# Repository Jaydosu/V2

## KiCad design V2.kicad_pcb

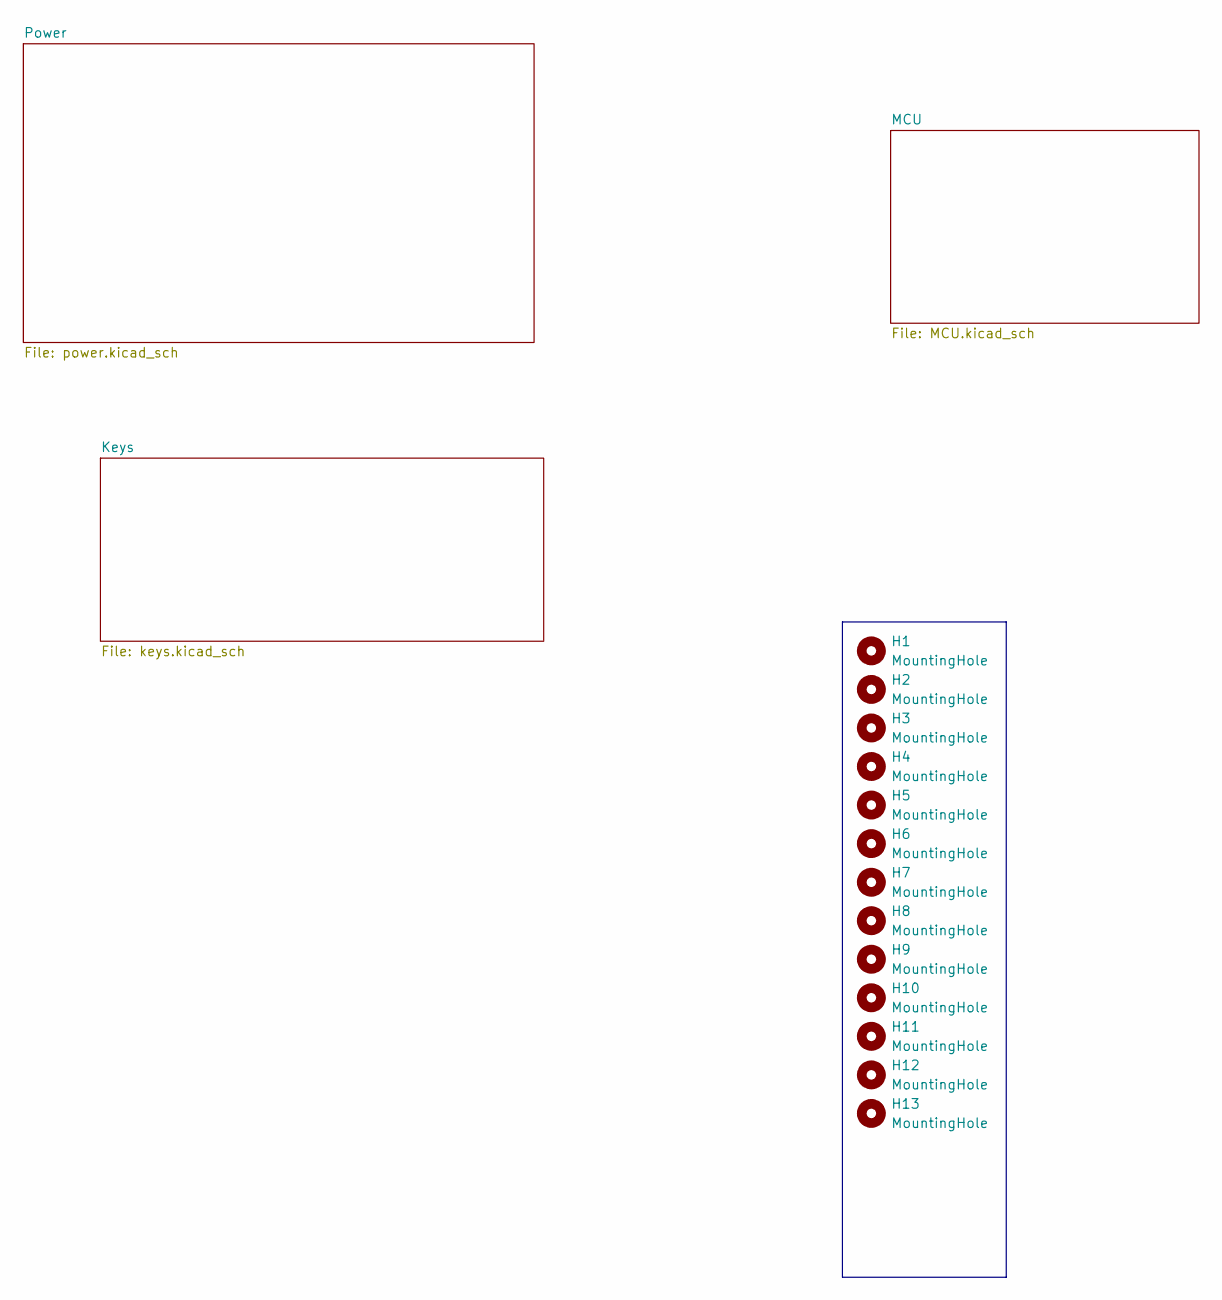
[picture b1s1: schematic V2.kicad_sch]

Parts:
H1, H2, H3, H4, H5, H6, H7, H8, H9, H10, H11, H12, H13: MountingHole; MountingHole_3.2mm_M3_Pad

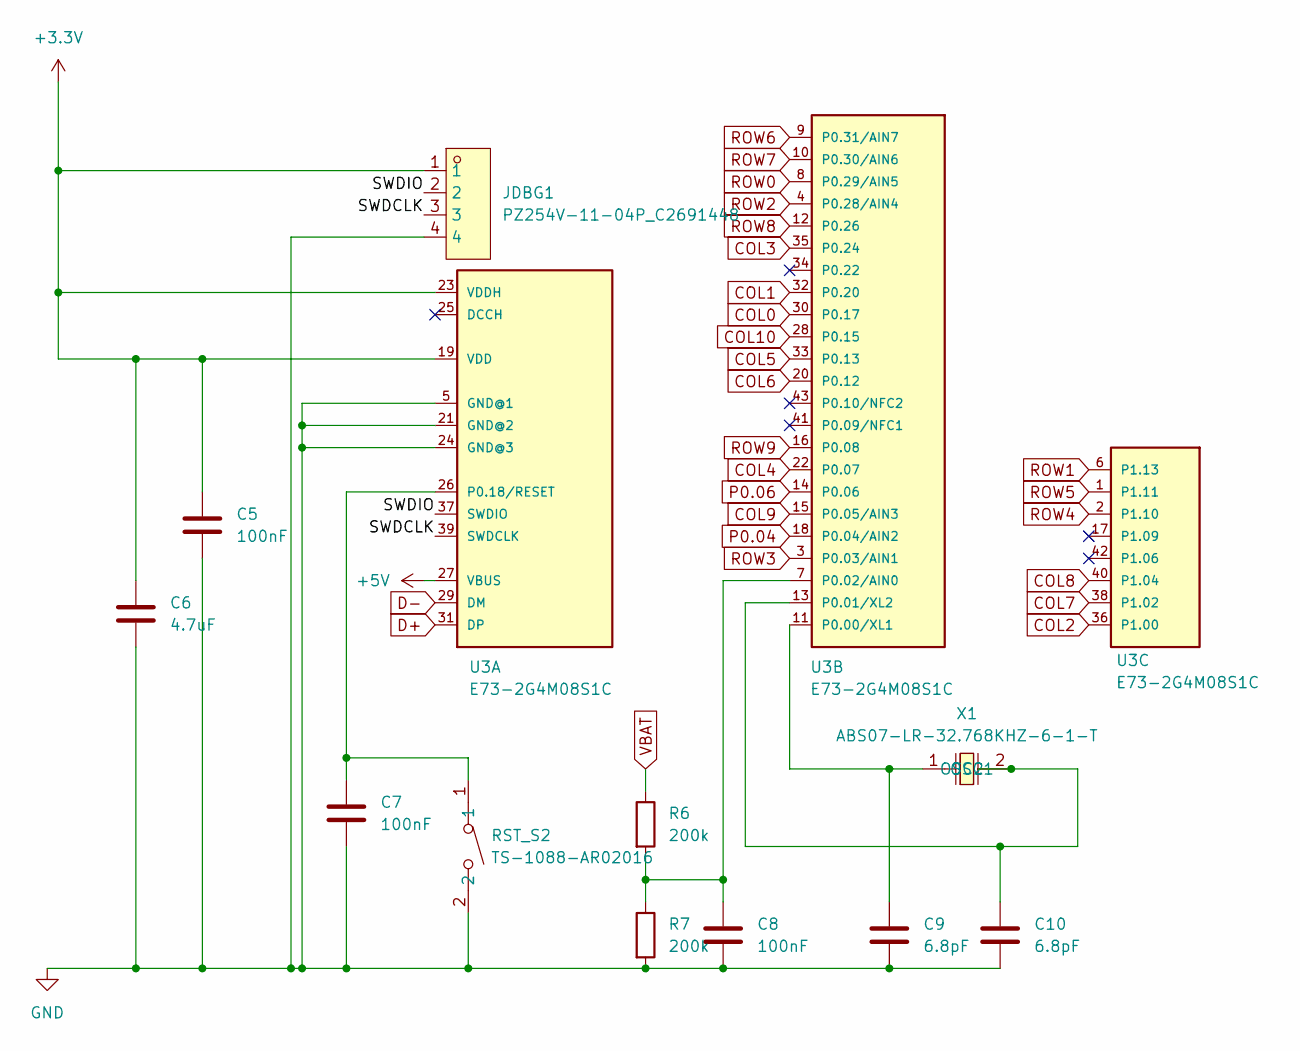
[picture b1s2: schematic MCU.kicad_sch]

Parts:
C5, C7, C8: 100nF; C_0603_1608Metric; LCSC Part C14663
C6: 4.7uF; C_0603_1608Metric; LCSC Part C19666
C9, C10: 6.8pF; C_0603_1608Metric; LCSC Part C1679
JDBG1: PZ254V-11-04P_C2691448; HDR-TH_4P-P2.54-V-M; MPN PZ254V-11-04P; LCSC Part C2691448
R6, R7: 200k; R_0603_1608Metric; LCSC Part C25811
RST_S2: TS-1088-AR02016; SW-SMD_L3.9-W3.0-P4.45; MPN TS-1088-AR02016; LCSC Part C720477
U3: E73-2G4M08S1C; LCSC Part C356849
X1: ABS07-LR-32.768KHZ-6-1-T; CRYSTAL-SMD_L3.2-W1.5; MPN ABS07-LR-32.768KHZ-6-1-T; LCSC Part C6491652

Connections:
+3.3V: C5.2, C6.1, JDBG1.1, U3.19 (VDD), U3.23 (VDDH); also elsewhere on the board
+5V: U3.27 (VBUS); also elsewhere on the board
/MCU/SWDCLK: JDBG1.3, U3.39 (SWDCLK)
/MCU/SWDIO: JDBG1.2, U3.37 (SWDIO)
COL0: U3.30 (P0.17); also elsewhere on the board
COL1: U3.32 (P0.20); also elsewhere on the board
COL2: U3.36 (P1.00); also elsewhere on the board
COL3: U3.35 (P0.24); also elsewhere on the board
COL4: U3.22 (P0.07); also elsewhere on the board
COL5: U3.33 (P0.13); also elsewhere on the board
COL6: U3.20 (P0.12); also elsewhere on the board
COL7: U3.38 (P1.02); also elsewhere on the board
COL8: U3.40 (P1.04); also elsewhere on the board
COL9: U3.15 (P0.05/AIN3); also elsewhere on the board
COL10: U3.28 (P0.15); also elsewhere on the board
D+: U3.31 (DP); also elsewhere on the board
D-: U3.29 (DM); also elsewhere on the board
GND: C5.1, C6.2, C7.2, C8.2, C9.2, C10.2, JDBG1.4, R7.2, RST_S2.2, U3.5 (GND@1), U3.21 (GND@2), U3.24 (GND@3); also elsewhere on the board
unnamed: C7.1, RST_S2.1, U3.26 (P0.18/RESET)
unnamed: C9.1, U3.11 (P0.00/XL1), X1.1 (OSC1)
unnamed: C10.1, U3.13 (P0.01/XL2), X1.2 (OSC2)
unnamed: C8.1, R6.2, R7.1, U3.7 (P0.02/AIN0)
P0.04: U3.18 (P0.04/AIN2); also elsewhere on the board
P0.06: U3.14 (P0.06); also elsewhere on the board
ROW0: U3.8 (P0.29/AIN5); also elsewhere on the board
ROW1: U3.6 (P1.13); also elsewhere on the board
ROW2: U3.4 (P0.28/AIN4); also elsewhere on the board
ROW3: U3.3 (P0.03/AIN1); also elsewhere on the board
ROW4: U3.2 (P1.10); also elsewhere on the board
ROW5: U3.1 (P1.11); also elsewhere on the board
ROW6: U3.9 (P0.31/AIN7); also elsewhere on the board
ROW7: U3.10 (P0.30/AIN6); also elsewhere on the board
ROW8: U3.12 (P0.26); also elsewhere on the board
ROW9: U3.16 (P0.08); also elsewhere on the board
VBAT: R6.1; also elsewhere on the board

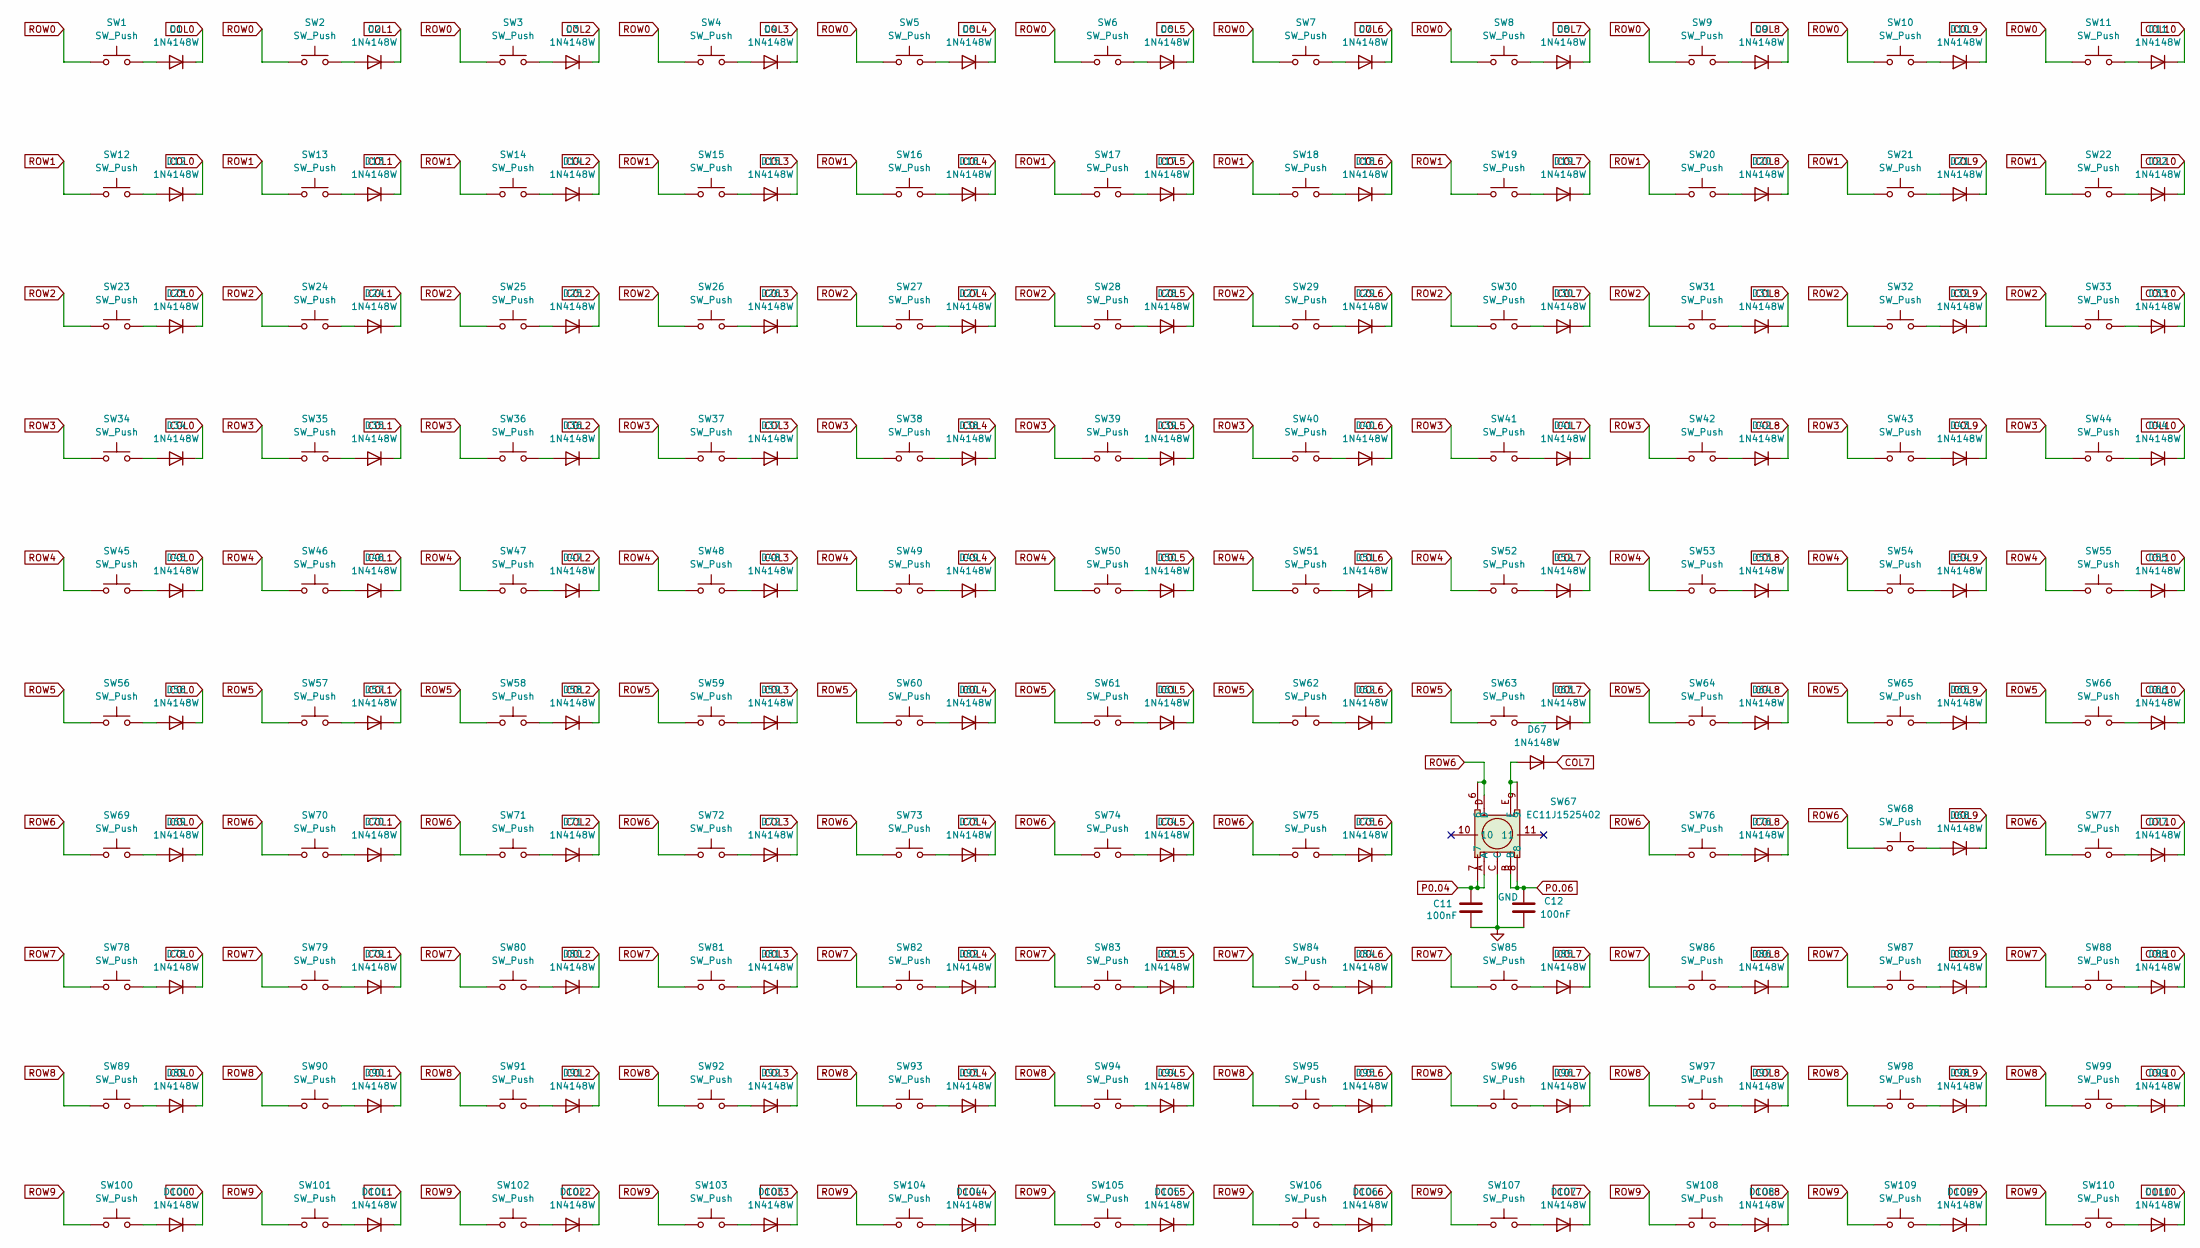
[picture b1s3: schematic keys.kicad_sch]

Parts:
C11, C12: 100nF; C_0603_1608Metric; LCSC Part C14663
D1, D2, D3, D4, D5, D6, D7, D8, D9, D10, D11, D12, D13, D14, D15, D16, D17, D18, D19, D20, D21, D22, D23, D24, D25, D26, D27, D28, D29, D30, D31, D32, D33, D34, D35, D36, D37, D38, D39, D40, D41, D42, D43, D44, D45, D46, D47, D48, D49, D50, D51, D52, D53, D54, D55, D56, D57, D58, D59, D60, D61, D62, D63, D64, D65, D66, D67, D68, D69, D70, D71, D72, D73, D74, D75, D76, D77, D78, D79, D80, D81, D82, D83, D84, D85, D86, D87, D88, D89, D90, D91, D92, D93, D94, D95, D96, D97, D98, D99, D100, D101, D102, D103, D104, D105, D106, D107, D108, D109, D110: 1N4148W; D_SOD-123; LCSC Part C81598
SW1, SW2, SW3, SW4, SW5, SW6, SW7, SW8, SW9, SW10, SW11, SW12, SW13, SW14, SW15, SW16, SW17, SW18, SW19, SW20, SW21, SW22, SW23, SW24, SW25, SW26, SW27, SW28, SW29, SW30, SW31, SW32, SW33, SW34, SW35, SW36, SW37, SW38, SW39, SW40, SW41, SW42, SW43, SW44, SW45, SW46, SW47, SW48, SW49, SW50, SW51, SW52, SW53, SW54, SW55, SW56, SW57, SW58, SW59, SW60, SW61, SW62, SW63, SW64, SW65, SW66, SW68, SW69, SW70, SW71, SW72, SW73, SW74, SW75, SW76, SW77, SW78, SW79, SW80, SW81, SW82, SW83, SW84, SW85, SW86, SW87, SW88, SW89, SW90, SW91, SW92, SW93, SW94, SW95, SW96, SW97, SW98, SW99, SW100, SW101, SW102, SW103, SW104, SW105, SW106, SW107, SW108, SW109, SW110: SW_Push; SW_Hotswap_Kailh_MX_Plated; LCSC Part C41430893
SW67: EC11J1525402; SW-SMD_EC11J1525402; MPN EC11J1525402; LCSC Part C209762

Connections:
COL0: D1.1 (K), D12.1 (K), D23.1 (K), D34.1 (K), D45.1 (K), D56.1 (K), D69.1 (K), D78.1 (K), D89.1 (K), D100.1 (K); also elsewhere on the board
COL1: D2.1 (K), D13.1 (K), D24.1 (K), D35.1 (K), D46.1 (K), D57.1 (K), D70.1 (K), D79.1 (K), D90.1 (K), D101.1 (K); also elsewhere on the board
COL2: D3.1 (K), D14.1 (K), D25.1 (K), D36.1 (K), D47.1 (K), D58.1 (K), D71.1 (K), D80.1 (K), D91.1 (K), D102.1 (K); also elsewhere on the board
COL3: D4.1 (K), D15.1 (K), D26.1 (K), D37.1 (K), D48.1 (K), D59.1 (K), D72.1 (K), D81.1 (K), D92.1 (K), D103.1 (K); also elsewhere on the board
COL4: D5.1 (K), D16.1 (K), D27.1 (K), D38.1 (K), D49.1 (K), D60.1 (K), D73.1 (K), D82.1 (K), D93.1 (K), D104.1 (K); also elsewhere on the board
COL5: D6.1 (K), D17.1 (K), D28.1 (K), D39.1 (K), D50.1 (K), D61.1 (K), D74.1 (K), D83.1 (K), D94.1 (K), D105.1 (K); also elsewhere on the board
COL6: D7.1 (K), D18.1 (K), D29.1 (K), D40.1 (K), D51.1 (K), D62.1 (K), D75.1 (K), D84.1 (K), D95.1 (K), D106.1 (K); also elsewhere on the board
COL7: D8.1 (K), D19.1 (K), D30.1 (K), D41.1 (K), D52.1 (K), D63.1 (K), D67.1 (K), D85.1 (K), D96.1 (K), D107.1 (K); also elsewhere on the board
COL8: D9.1 (K), D20.1 (K), D31.1 (K), D42.1 (K), D53.1 (K), D64.1 (K), D76.1 (K), D86.1 (K), D97.1 (K), D108.1 (K); also elsewhere on the board
COL9: D10.1 (K), D21.1 (K), D32.1 (K), D43.1 (K), D54.1 (K), D65.1 (K), D68.1 (K), D87.1 (K), D98.1 (K), D109.1 (K); also elsewhere on the board
COL10: D11.1 (K), D22.1 (K), D33.1 (K), D44.1 (K), D55.1 (K), D66.1 (K), D77.1 (K), D88.1 (K), D99.1 (K), D110.1 (K); also elsewhere on the board
GND: C11.2, C12.2, SW67.C; also elsewhere on the board
unnamed: D1.2 (A), SW1.2
unnamed: D2.2 (A), SW2.2
unnamed: D3.2 (A), SW3.2
unnamed: D4.2 (A), SW4.2
unnamed: D5.2 (A), SW5.2
unnamed: D6.2 (A), SW6.2
unnamed: D7.2 (A), SW7.2
unnamed: D8.2 (A), SW8.2
unnamed: D9.2 (A), SW9.2
unnamed: D10.2 (A), SW10.2
unnamed: D11.2 (A), SW11.2
unnamed: D12.2 (A), SW12.2
unnamed: D13.2 (A), SW13.2
unnamed: D14.2 (A), SW14.2
unnamed: D15.2 (A), SW15.2
unnamed: D16.2 (A), SW16.2
unnamed: D17.2 (A), SW17.2
unnamed: D18.2 (A), SW18.2
unnamed: D19.2 (A), SW19.2
unnamed: D20.2 (A), SW20.2
unnamed: D21.2 (A), SW21.2
unnamed: D22.2 (A), SW22.2
unnamed: D23.2 (A), SW23.2
unnamed: D24.2 (A), SW24.2
unnamed: D25.2 (A), SW25.2
unnamed: D26.2 (A), SW26.2
unnamed: D27.2 (A), SW27.2
unnamed: D28.2 (A), SW28.2
unnamed: D29.2 (A), SW29.2
unnamed: D30.2 (A), SW30.2
unnamed: D31.2 (A), SW31.2
unnamed: D32.2 (A), SW32.2
unnamed: D33.2 (A), SW33.2
unnamed: D34.2 (A), SW34.2
unnamed: D35.2 (A), SW35.2
unnamed: D36.2 (A), SW36.2
unnamed: D37.2 (A), SW37.2
unnamed: D38.2 (A), SW38.2
unnamed: D39.2 (A), SW39.2
unnamed: D40.2 (A), SW40.2
unnamed: D41.2 (A), SW41.2
unnamed: D42.2 (A), SW42.2
unnamed: D43.2 (A), SW43.2
unnamed: D44.2 (A), SW44.2
unnamed: D45.2 (A), SW45.2
unnamed: D46.2 (A), SW46.2
unnamed: D47.2 (A), SW47.2
unnamed: D48.2 (A), SW48.2
unnamed: D49.2 (A), SW49.2
unnamed: D50.2 (A), SW50.2
unnamed: D51.2 (A), SW51.2
unnamed: D52.2 (A), SW52.2
unnamed: D53.2 (A), SW53.2
unnamed: D54.2 (A), SW54.2
unnamed: D55.2 (A), SW55.2
unnamed: D56.2 (A), SW56.2
unnamed: D57.2 (A), SW57.2
unnamed: D58.2 (A), SW58.2
unnamed: D59.2 (A), SW59.2
unnamed: D60.2 (A), SW60.2
unnamed: D61.2 (A), SW61.2
unnamed: D62.2 (A), SW62.2
unnamed: D63.2 (A), SW63.2
unnamed: D64.2 (A), SW64.2
unnamed: D65.2 (A), SW65.2
unnamed: D66.2 (A), SW66.2
unnamed: D67.2 (A), SW67.9, SW67.E
unnamed: D68.2 (A), SW68.2
unnamed: D69.2 (A), SW69.2
unnamed: D70.2 (A), SW70.2
unnamed: D71.2 (A), SW71.2
unnamed: D72.2 (A), SW72.2
unnamed: D73.2 (A), SW73.2
unnamed: D74.2 (A), SW74.2
unnamed: D75.2 (A), SW75.2
unnamed: D76.2 (A), SW76.2
unnamed: D77.2 (A), SW77.2
unnamed: D78.2 (A), SW78.2
unnamed: D79.2 (A), SW79.2
unnamed: D80.2 (A), SW80.2
unnamed: D81.2 (A), SW81.2
unnamed: D82.2 (A), SW82.2
unnamed: D83.2 (A), SW83.2
unnamed: D84.2 (A), SW84.2
unnamed: D85.2 (A), SW85.2
unnamed: D86.2 (A), SW86.2
unnamed: D87.2 (A), SW87.2
unnamed: D88.2 (A), SW88.2
unnamed: D89.2 (A), SW89.2
unnamed: D90.2 (A), SW90.2
unnamed: D91.2 (A), SW91.2
unnamed: D92.2 (A), SW92.2
unnamed: D93.2 (A), SW93.2
unnamed: D94.2 (A), SW94.2
unnamed: D95.2 (A), SW95.2
unnamed: D96.2 (A), SW96.2
unnamed: D97.2 (A), SW97.2
unnamed: D98.2 (A), SW98.2
unnamed: D99.2 (A), SW99.2
unnamed: D100.2 (A), SW100.2
unnamed: D101.2 (A), SW101.2
unnamed: D102.2 (A), SW102.2
unnamed: D103.2 (A), SW103.2
unnamed: D104.2 (A), SW104.2
unnamed: D105.2 (A), SW105.2
unnamed: D106.2 (A), SW106.2
unnamed: D107.2 (A), SW107.2
unnamed: D108.2 (A), SW108.2
unnamed: D109.2 (A), SW109.2
unnamed: D110.2 (A), SW110.2
P0.04: C11.1, SW67.7, SW67.A; also elsewhere on the board
P0.06: C12.1, SW67.8, SW67.B; also elsewhere on the board
ROW0: SW1.1, SW2.1, SW3.1, SW4.1, SW5.1, SW6.1, SW7.1, SW8.1, SW9.1, SW10.1, SW11.1; also elsewhere on the board
ROW1: SW12.1, SW13.1, SW14.1, SW15.1, SW16.1, SW17.1, SW18.1, SW19.1, SW20.1, SW21.1, SW22.1; also elsewhere on the board
ROW2: SW23.1, SW24.1, SW25.1, SW26.1, SW27.1, SW28.1, SW29.1, SW30.1, SW31.1, SW32.1, SW33.1; also elsewhere on the board
ROW3: SW34.1, SW35.1, SW36.1, SW37.1, SW38.1, SW39.1, SW40.1, SW41.1, SW42.1, SW43.1, SW44.1; also elsewhere on the board
ROW4: SW45.1, SW46.1, SW47.1, SW48.1, SW49.1, SW50.1, SW51.1, SW52.1, SW53.1, SW54.1, SW55.1; also elsewhere on the board
ROW5: SW56.1, SW57.1, SW58.1, SW59.1, SW60.1, SW61.1, SW62.1, SW63.1, SW64.1, SW65.1, SW66.1; also elsewhere on the board
ROW6: SW67.6, SW67.D, SW68.1, SW69.1, SW70.1, SW71.1, SW72.1, SW73.1, SW74.1, SW75.1, SW76.1, SW77.1; also elsewhere on the board
ROW7: SW78.1, SW79.1, SW80.1, SW81.1, SW82.1, SW83.1, SW84.1, SW85.1, SW86.1, SW87.1, SW88.1; also elsewhere on the board
ROW8: SW89.1, SW90.1, SW91.1, SW92.1, SW93.1, SW94.1, SW95.1, SW96.1, SW97.1, SW98.1, SW99.1; also elsewhere on the board
ROW9: SW100.1, SW101.1, SW102.1, SW103.1, SW104.1, SW105.1, SW106.1, SW107.1, SW108.1, SW109.1, SW110.1; also elsewhere on the board

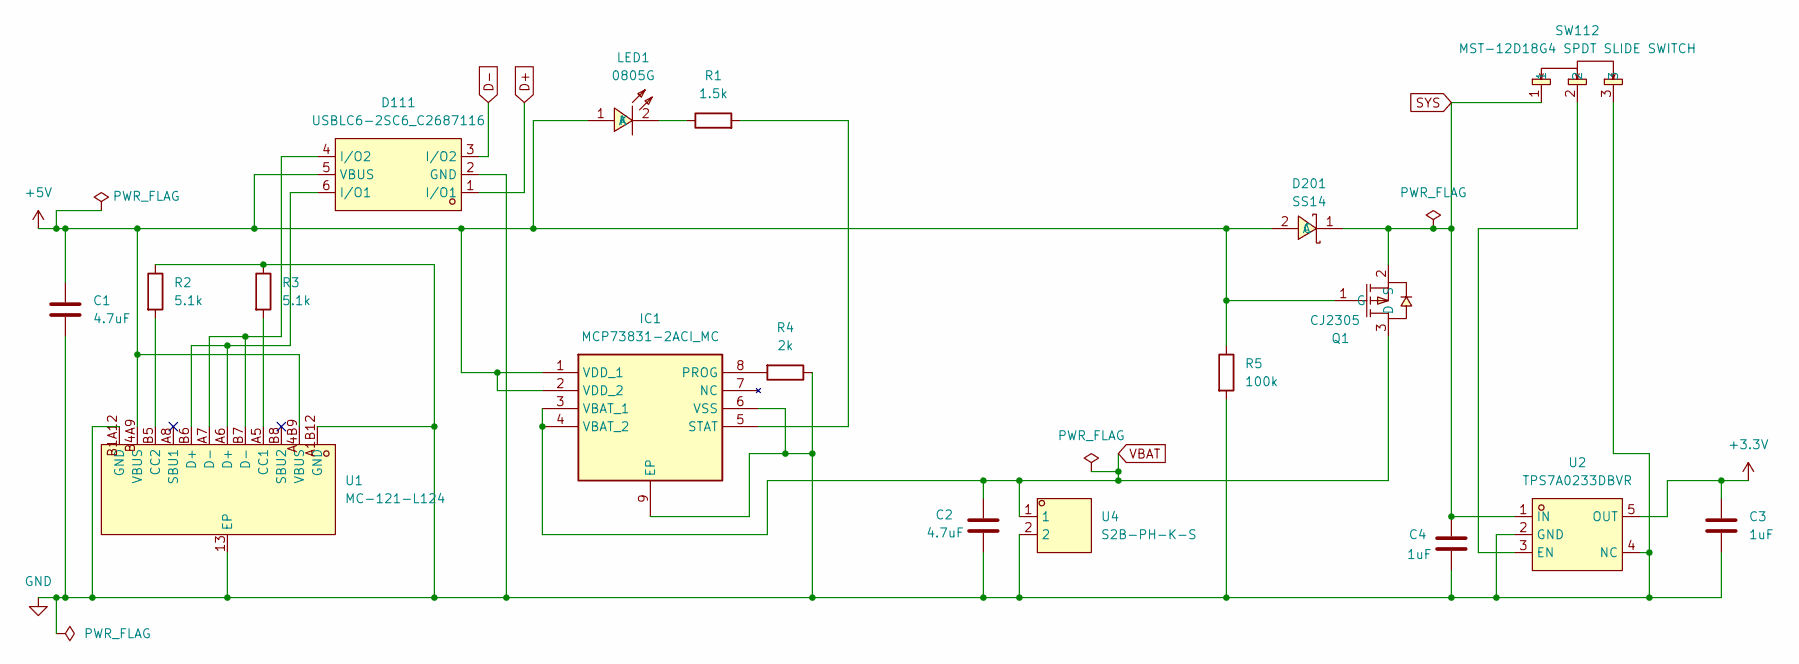
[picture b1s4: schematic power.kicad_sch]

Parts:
C1, C2: 4.7uF; C_0603_1608Metric; LCSC Part C19666
C3, C4: 1uF; C_0603_1608Metric; LCSC Part C15849
D111: USBLC6-2SC6_C2687116; SOT-23-6_L2.9-W1.6-P0.95-LS2.8-BL; MPN USBLC6-2SC6; LCSC Part C2687116
D201: SS14; SMA_L4.2-W2.6-LS5.3-RD; MPN SS14; LCSC Part C2480
IC1: MCP73831-2ACI_MC; DFN8_2x3MC_MCH; Manufacturer_Part_Number MCP73831-2ACI/MC; Mouser Part Number 579-MCP73831-2ACI/MC
LED1: 0805G; LED0805-R-RD; MPN KT-0805G; LCSC Part C2297
Q1: CJ2305; SOT-23-3_L2.9-W1.3-P1.90-LS2.4-BR; MPN CJ2305; LCSC Part C8549
R1: 1.5k; R_0603_1608Metric; LCSC Part C22843
R2, R3: 5.1k; R_0603_1608Metric; LCSC Part C23186
R4: 2k; R_0603_1608Metric; LCSC Part C22975
R5: 100k; R_0603_1608Metric; LCSC Part C25803
SW112: MST-12D18G4 SPDT SLIDE SWITCH; SW-SMD_MST-12D18G4-SPDT-SLIDE-SWITCH; MPN MST-12D18G4 SPDT Slide Switch; LCSC Part C49023767
U1: MC-121-L124; USB-C-SMD_HANBO_MC-121-L124; MPN MC-121-L124; LCSC Part C6332279
U2: TPS7A0233DBVR; SOT-23-5_L2.9-W1.6-P0.95-LS2.8-BL; MPN TPS7A0233DBVR; LCSC Part C5142805
U4: S2B-PH-K-S; CONN-TH_S2B-PH-K-S-LF-SN; MPN S2B-PH-K-S(LF)(SN); LCSC Part C173752

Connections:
+3.3V: C3.2, U2.5 (OUT); also elsewhere on the board
+5V: C1.1, D111.5 (VBUS), D201.2 (A), IC1.1 (VDD_1), IC1.2 (VDD_2), LED1.1 (A), Q1.1 (G), R5.1, U1.A4B9 (VBUS), U1.B4A9 (VBUS); also elsewhere on the board
D+: D111.1 (I/O1); also elsewhere on the board
D-: D111.3 (I/O2); also elsewhere on the board
GND: C1.2, C2.2, C3.1, C4.1, D111.2 (GND), IC1.6 (VSS), IC1.9 (EP), R2.1, R3.1, R4.1, R5.2, SW112.3, U1.13 (EP), U1.A1B12 (GND), U1.B1A12 (GND), U2.2 (GND), U2.4 (NC), U4.2; also elsewhere on the board
unnamed: D111.6 (I/O1), U1.A6 (D+), U1.B6 (D+)
unnamed: D111.4 (I/O2), U1.A7 (D-), U1.B7 (D-)
unnamed: IC1.8 (PROG), R4.2
unnamed: IC1.5 (STAT), R1.2
unnamed: LED1.2 (K), R1.1
unnamed: R3.2, U1.A5 (CC1)
unnamed: R2.2, U1.B5 (CC2)
unnamed: SW112.2, U2.3 (EN)
SYS: C4.2, D201.1 (C), Q1.2 (S), SW112.1, U2.1 (IN)
VBAT: C2.1, IC1.3 (VBAT_1), IC1.4 (VBAT_2), Q1.3 (D), U4.1; also elsewhere on the board

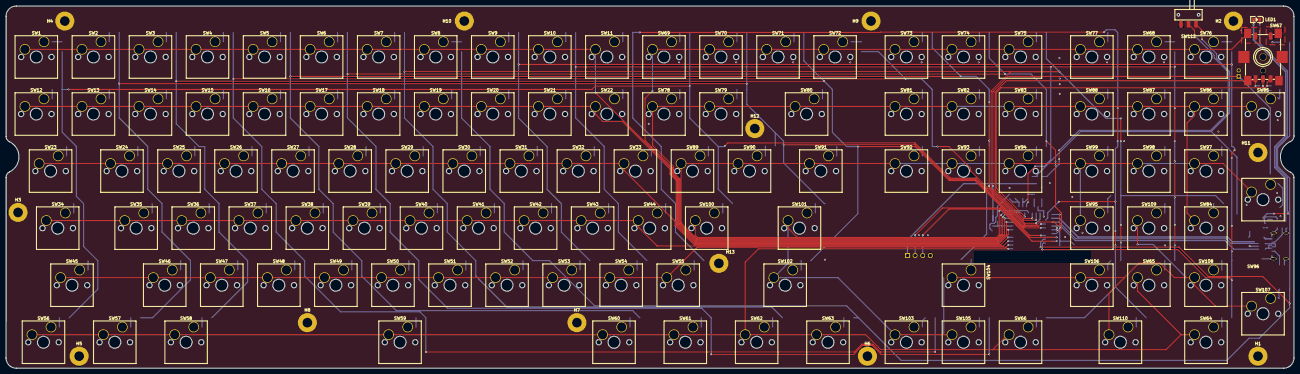
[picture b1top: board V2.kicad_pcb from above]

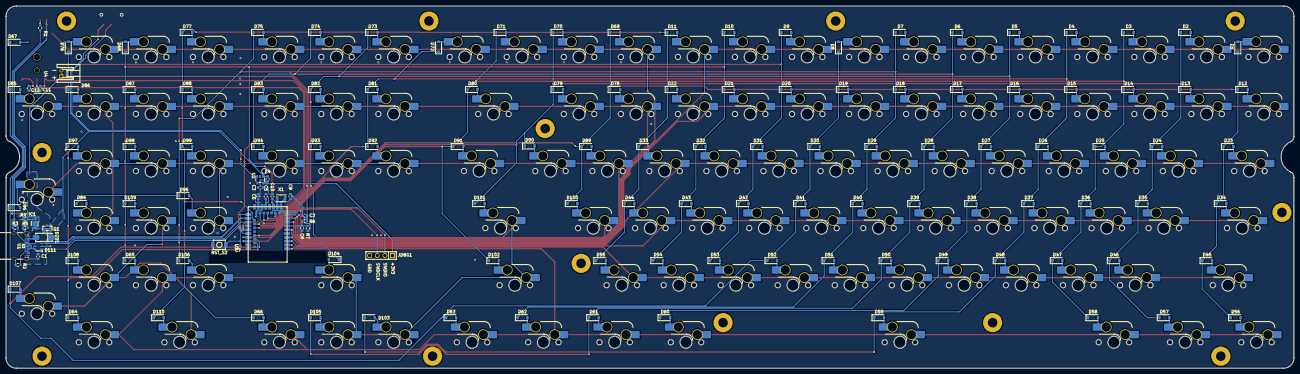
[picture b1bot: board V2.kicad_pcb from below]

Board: 2 copper layers, 430.0 x 120.9 mm, 265 parts (140 on the bottom side), 154 nets.

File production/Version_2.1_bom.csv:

Designator,Footprint,Quantity,Value,LCSC Part #
"C1, C2, C6",0603,3,4.7uF,C19666
"C10, C9",0603,2,6.8pF,C1679
"C11, C12, C5, C7, C8",0603,5,100nF,C14663
"C3, C4",0603,2,1uF,C15849
"D1, D10, D100, D101, D102, D103, D104, D105, D106, D107, D108, D109, D11, D110, D12, D13, D14, D15, D16, D17, D18, D19, D2, D20, D21, D22, D23, D24, D25, D26, D27, D28, D29, D3, D30, D31, D32, D33, D34, D35, D36, D37, D38, D39, D4, D40, D41, D42, D43, D44, D45, D46, D47, D48, D49, D5, D50, D51, D52, D53, D54, D55, D56, D57, D58, D59, D6, D60, D61, D62, D63, D64, D65, D66, D67, D68, D69, D7, D70, D71, D72, D73, D74, D75, D76, D77, D78, D79, D8, D80, D81, D82, D83, D84, D85, D86, D87, D88, D89, D9, D90, D91, D92, D93, D94, D95, D96, D97, D98, D99",D_SOD-123,110,1N4148W,C81598
D111,SOT-23-6_L2.9-W1.6-P0.95-LS2.8-BL,1,USBLC6-2SC6_C2687116,C2687116
D201,SMA_L4.2-W2.6-LS5.3-RD,1,SS14,C2480
IC1,DFN8_2x3MC_MCH,1,MCP73831-2ACI_MC,C150772
JDBG1,HDR-TH_4P-P2.54-V-M,1,PZ254V-11-04P_C2691448,C2691448
LED1,LED0805-R-RD,1,0805G,C2297
PWR_S1,SW-TH_MSK12C02,1,MSK12C02,C431540
Q1,SOT-23-3_L2.9-W1.3-P1.90-LS2.4-BR,1,CJ2305,C8549
R1,0603,1,1.5k,C22843
"R2, R3",0603,2,5.1k,C23186
R4,0603,1,2k,C22975
R5,0603,1,100k,C25803
"R6, R7",0603,2,200k,C25811
RST_S2,SW-SMD_L3.9-W3.0-P4.45,1,TS-1088-AR02016,C720477
"SW1, SW10, SW100, SW101, SW102, SW103, SW104, SW105, SW106, SW107, SW108, SW109, SW11, SW110, SW12, SW13, SW14, SW15, SW16, SW17, SW18, SW19, SW2, SW20, SW21, SW22, SW23, SW24, SW25, SW26, SW27, SW28, SW29, SW3, SW30, SW31, SW32, SW33, SW34, SW35, SW36, SW37, SW38, SW39, SW4, SW40, SW41, SW42, SW43, SW44, SW45, SW46, SW47, SW48, SW49, SW5, SW50, SW51, SW52, SW53, SW54, SW55, SW56, SW57, SW58, SW59, SW6, SW60, SW61, SW62, SW63, SW64, SW65, SW66, SW68, SW69, SW7, SW70, SW71, SW72, SW73, SW74, SW75, SW76, SW77, SW78, SW79, SW8, SW80, SW81, SW82, SW83, SW84, SW85, SW86, SW87, SW88, SW89, SW9, SW90, SW91, SW92, SW93, SW94, SW95, SW96, SW97, SW98, SW99",SW_Hotswap_Kailh_MX_Plated,109,SW_Push,C41430893
SW67,SW-SMD_EC11J1525402,1,EC11J1525402,C209762
U1,USB-C-SMD_HANBO_MC-121-L124,1,MC-121-L124,C6332279
U2,SOT-23-5_L2.9-W1.6-P0.95-LS2.8-BL,1,TPS7A0233DBVR,C5142805
U3,E73-2G4M08S1C,1,E73-2G4M08S1C,C356849
U4,CONN-TH_S2B-PH-K-S-LF-SN,1,S2B-PH-K-S,C173752
X1,CRYSTAL-SMD_L3.2-W1.5,1,ABS07-LR-32.768KHZ-6-1-T,C6491652
